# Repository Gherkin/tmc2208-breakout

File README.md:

# A breakout board for TMC2208-LA

ibom: https://gherkin.github.io/tmc2208-breakout/

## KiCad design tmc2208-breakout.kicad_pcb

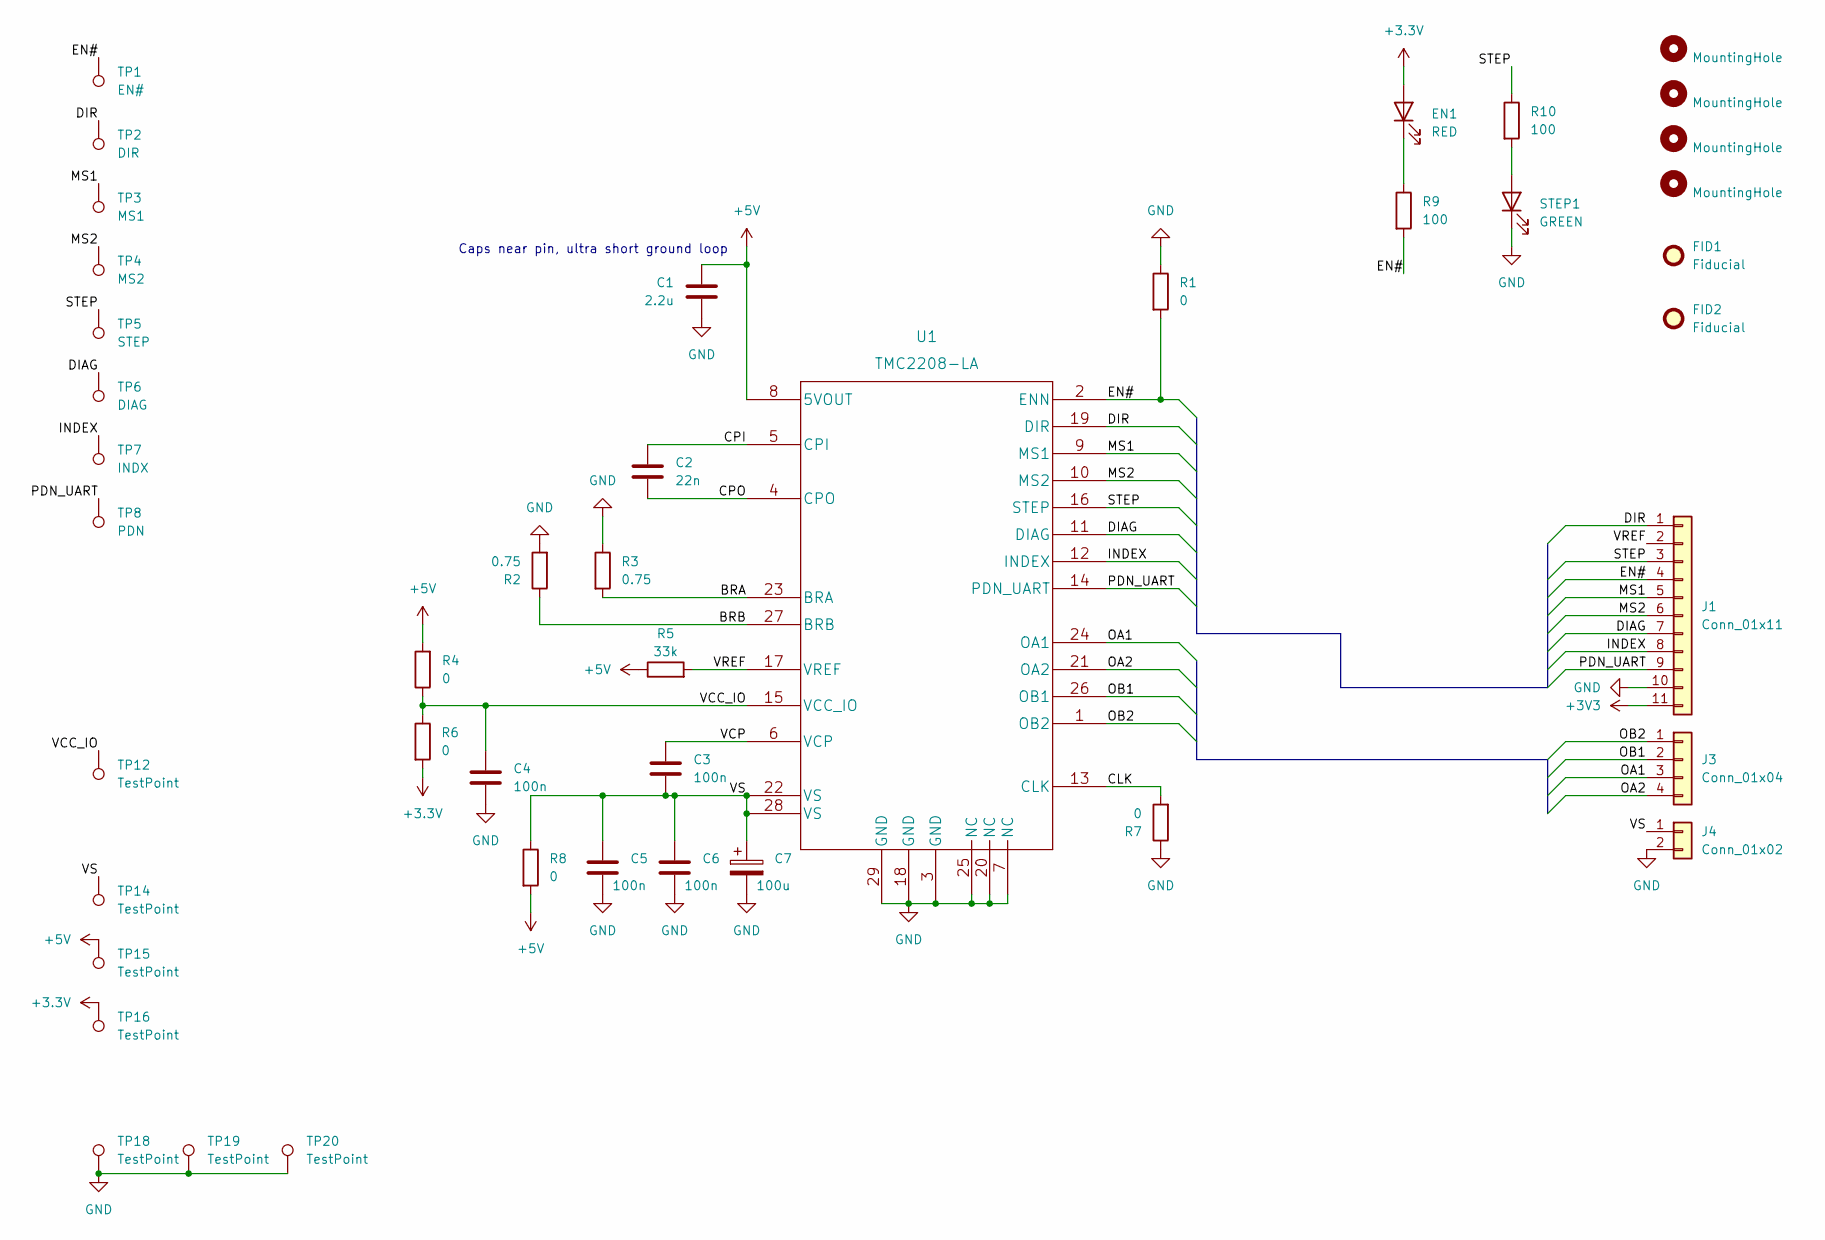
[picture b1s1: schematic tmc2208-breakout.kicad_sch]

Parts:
C1: 2.2u; C_0603_1608Metric_Pad1.08x0.95mm_HandSolder; LCSC C23630
C2: 22n; C_0603_1608Metric_Pad1.08x0.95mm_HandSolder; LCSC C106222
C3, C4, C5, C6: 100n; C_0603_1608Metric_Pad1.08x0.95mm_HandSolder; LCSC C1591
C7: 100u; CP_Elec_6.3x5.4; LCSC C129250
EN1: RED; LED_1206_3216Metric_Pad1.42x1.75mm_HandSolder
FID1, FID2: Fiducial; Fiducial_0.5mm_Mask1.5mm
H1, H2, H3, H4: MountingHole; MountingHole_2.2mm_M2
J1: Conn_01x11; PinHeader_1x11_P2.54mm_Vertical; LCSC C429959
J3: Conn_01x04; JST_XH_B4B-XH-A_1x04_P2.50mm_Vertical; LCSC C144395
J4: Conn_01x02; TerminalBlock_Phoenix_MKDS-1,5-2_1x02_P5.00mm_Horizontal; LCSC C8404
R1, R4, R6, R7, R8: 0; R_0603_1608Metric_Pad0.98x0.95mm_HandSolder; LCSC C100044
R2, R3: 0.75; R_0603_1608Metric_Pad0.98x0.95mm_HandSolder; LCSC C175689
R5: 33k; R_0603_1608Metric_Pad0.98x0.95mm_HandSolder; LCSC C25593
R9, R10: 100; R_0603_1608Metric_Pad0.98x0.95mm_HandSolder
STEP1: GREEN; LED_1206_3216Metric_Pad1.42x1.75mm_HandSolder
TP1: EN#; TestPoint_THTPad_D1.0mm_Drill0.5mm
TP2: DIR; TestPoint_THTPad_D1.0mm_Drill0.5mm
TP3: MS1; TestPoint_THTPad_D1.0mm_Drill0.5mm
TP4: MS2; TestPoint_THTPad_D1.0mm_Drill0.5mm
TP5: STEP; TestPoint_THTPad_D1.0mm_Drill0.5mm
TP6: DIAG; TestPoint_THTPad_D1.0mm_Drill0.5mm
TP7: INDX; TestPoint_THTPad_D1.0mm_Drill0.5mm
TP8: PDN; TestPoint_THTPad_D1.0mm_Drill0.5mm
TP12, TP14, TP15, TP16: TestPoint; TestPoint_THTPad_D1.0mm_Drill0.5mm
TP18, TP19, TP20: TestPoint; TestPoint_THTPad_1.0x1.0mm_Drill0.5mm
U1: TMC2208-LA; LCSC C115944

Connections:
+5V: C1.1, R4.2, R5.1, R8.2, TP15.1, U1.8 (5VOUT)
/BRA: R3.2, U1.23 (BRA)
/BRB: R2.1, U1.27 (BRB)
/CLK: R7.2, U1.13 (CLK)
/CPI: C2.1, U1.5 (CPI)
/CPO: C2.2, U1.4 (CPO)
/DIAG: J1.7, TP6.1, U1.11 (DIAG)
/DIR: J1.1, TP2.1, U1.19 (DIR)
/EN#: J1.4, R1.2, R9.2, TP1.1, U1.2 (ENN)
/INDEX: J1.8, TP7.1, U1.12 (INDEX)
/MS1: J1.5, TP3.1, U1.9 (MS1)
/MS2: J1.6, TP4.1, U1.10 (MS2)
/OA1: J3.3, U1.24 (OA1)
/OA2: J3.4, U1.21 (OA2)
/OB1: J3.2, U1.26 (OB1)
/OB2: J3.1, U1.1 (OB2)
/PDN_UART: J1.9, TP8.1, U1.14 (PDN_UART)
/STEP: J1.3, R10.1, TP5.1, U1.16 (STEP)
/VCC_IO: C4.1, R4.1, R6.1, TP12.1, U1.15 (VCC_IO)
/VCP: C3.1, U1.6 (VCP)
/VREF: J1.2, R5.2, U1.17 (VREF)
/VS: C3.2, C5.1, C6.1, C7.1, J4.1, R8.1, TP14.1, U1.22 (VS), U1.28 (VS)
GND: C1.2, C4.2, C5.2, C6.2, C7.2, J1.10, J4.2, R1.1, R2.2, R3.1, R7.1, STEP1.1 (K), TP18.1, TP19.1, TP20.1, U1.3 (GND), U1.7 (NC), U1.18 (GND), U1.20 (NC), U1.25 (NC), U1.29 (GND)
unnamed: EN1.1 (K), R9.1
unnamed: R10.2, STEP1.2 (A)

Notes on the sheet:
Caps near pin, ultra short ground loop

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
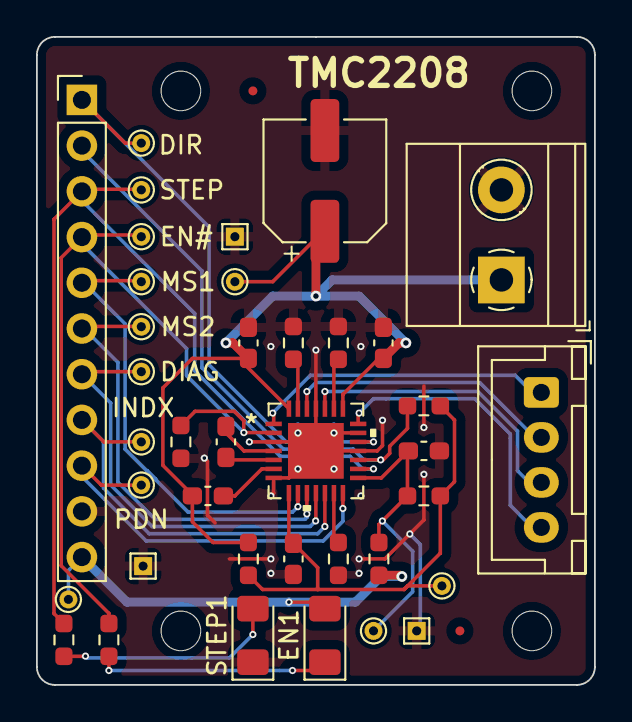
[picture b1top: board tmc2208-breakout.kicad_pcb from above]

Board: 2 copper layers, 31.0 x 36.0 mm, 44 parts (0 on the bottom side), 26 nets.

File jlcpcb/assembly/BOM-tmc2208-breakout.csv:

Comment,Designator,Footprint,LCSC
0,"R1,R4,R6,R7,R8",R_0603_1608Metric_Pad0.98x0.95mm_HandSolder,C100044
100,"R10,R9",R_0603_1608Metric_Pad0.98x0.95mm_HandSolder,C105588
22n,C2,C_0603_1608Metric_Pad1.08x0.95mm_HandSolder,C106222
TMC2208-LA,U1,TMC2208-LA,C115944
100u,C7,CP_Elec_6.3x5.4,C129250
Conn_01x04,J3,JST_XH_B4B-XH-A_1x04_P2.50mm_Vertical,C144395
100n,"C3,C4,C5,C6",C_0603_1608Metric_Pad1.08x0.95mm_HandSolder,C1591
0.75,"R2,R3",R_0603_1608Metric_Pad0.98x0.95mm_HandSolder,C175689
2.2u,C1,C_0603_1608Metric_Pad1.08x0.95mm_HandSolder,C23630
33k,R5,R_0603_1608Metric_Pad0.98x0.95mm_HandSolder,C25593
Conn_01x11,J1,PinHeader_1x11_P2.54mm_Vertical,C429959
Conn_01x02,J4,"TerminalBlock_Phoenix_MKDS-1,5-2_1x02_P5.00mm_Horizontal",C8404
GREEN,STEP1,LED_1206_3216Metric_Pad1.42x1.75mm_HandSolder,C84273
RED,EN1,LED_1206_3216Metric_Pad1.42x1.75mm_HandSolder,C93133

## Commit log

2022-06-26 init
2022-06-26 preparing release
2022-06-26 added ibom
2022-06-26 added readme
2022-06-26 changed some minor things like connector and finalized bom for v1.0
2022-06-26 added lcsc field to components for ibom, also changed r5 to 33k
2022-06-26 removed J1 designator from silkscreen
2022-06-27 added LEDs for EN# and STEP
2022-06-27 added image
2025-03-29 a stencil i had forgot to commit

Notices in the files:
parts and their libraries:
Copyright 2021 Accelerated Designs. All rights reserved.
